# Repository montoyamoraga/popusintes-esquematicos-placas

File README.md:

# popusintes-esquematicos-placas

Parte de la tesis de Aarón Montoya-Moraga, en el Doctorado de Artes y Humanidades del Instituto de Estudios Avanzados de la Universidad de Santiago de Chile.

## Módulos

- [ataconso](./docs/ataconso.md)
- [chufe](./docs/chufe.md)
- [chufebu](./docs/chufebu.md)
- [diente](./docs/diente.md)
- [parla](./docs/parla.md)
- [relo](./docs/relo.md)
- [suma](https://github.com/piruetasxyz/suma): ahora en su propio repositorio.

## Desarrollo

Los esquemáticos y placas están hechos en KiCad. Para regenerar los BOM u otras exportaciones se usa un entorno virtual de Python:

```bash
python3 -m venv env
source env/bin/activate
pip install -r requirements.txt
```

`env/` está en `.gitignore`, así que hay que crearlo localmente antes de correr herramientas como `kicad-cli` o `easyeda2kicad`.

## Capturas y Bill of materials

Las capturas de esquemáticos y placas en [docs/images](./docs/images) y las tablas de Bill of materials en `docs/*.md` las genera [kicad-retrata](https://github.com/piruetasxyz/kicad-retrata) con GitHub Actions en cada push que cambia un archivo de KiCad. Los módulos y su revisión activa se configuran en [kicad-retrata.yml](./kicad-retrata.yml): para pasar un módulo a una nueva revisión basta con cambiar su `proyecto` ahí.

## Bibliotecas

Las bibliotecas de KiCad (símbolos, huellas y modelos 3D) están en [bibliotecas](./bibliotecas):

- [byom](./bibliotecas/byom): biblioteca BYOM (símbolos, huellas y modelos 3D de terceros).
- [easyeda2kicad.kicad_sym](./bibliotecas/easyeda2kicad.kicad_sym), [easyeda2kicad.pretty](./bibliotecas/easyeda2kicad.pretty) y [easyeda2kicad.3dshapes](./bibliotecas/easyeda2kicad.3dshapes): símbolos, huellas y modelos 3D convertidos desde EasyEDA con `easyeda2kicad`.

Hay que agregar `bibliotecas` como ruta de biblioteca en KiCad (Preferencias → Administrar bibliotecas de símbolos/huellas) para que los esquemáticos y placas encuentren estas piezas.

## Bloques reutilizables

[popusintes.kicad_blocks](./bibliotecas/popusintes.kicad_blocks) es una biblioteca de bloques de diseño (design blocks) de KiCad 10: fragmentos de circuito que se copian dentro de cada módulo, en vez de enlazarlos como hoja jerárquica compartida. Cada módulo queda con su propia copia, congelada en la versión con que se fabricó, así que cambiar un bloque no altera las revisiones ya hechas.

- [alimentacion-12v](./bibliotecas/popusintes.kicad_blocks/alimentacion-12v.kicad_block): conector eurorack 2x05 y diodos Schottky de protección contra polaridad inversa en ±12V.
- [alimentacion-12v-5v](./bibliotecas/popusintes.kicad_blocks/alimentacion-12v-5v.kicad_block): por ahora idéntico a `alimentacion-12v`; pensado para agregarle la rama de +5V.

Para usarlos:

1. Registrar la biblioteca en Preferencias → Administrar bibliotecas de bloques de diseño. La [plantilla](./plantillas/kicad/plantilla-popusintes) ya trae una tabla de proyecto (`design-block-lib-table`) que apunta a `${KIPRJMOD}/../../bibliotecas/popusintes.kicad_blocks`, válida para proyectos ubicados en `<modulo>/<modulo>-v-X-rev-Y/`.
2. En el editor de esquemáticos, abrir el panel de bloques de diseño y colocar el bloque, ya sea en línea o como hoja (_place as sheet_).
3. Para agregar o actualizar un bloque, seleccionar el circuito en un esquemático y guardarlo en la biblioteca desde el mismo panel.

Ataconso, que usaba la hoja compartida antigua, ahora tiene en [ataconso-v-0-rev-c](./ataconso/ataconso-v-0-rev-c) su propia copia de `fuente-alimentacion.kicad_sch` junto al proyecto. Parla y relo tienen la fuente de alimentación dibujada directamente en el esquemático.

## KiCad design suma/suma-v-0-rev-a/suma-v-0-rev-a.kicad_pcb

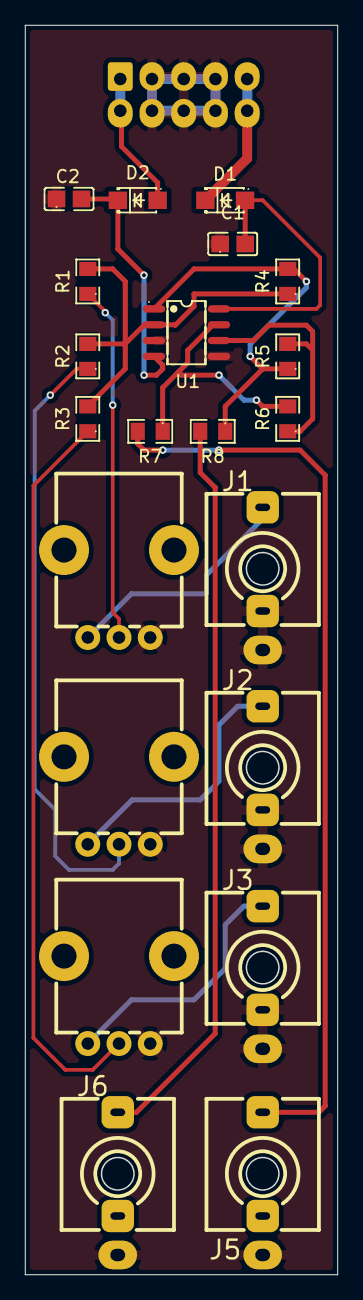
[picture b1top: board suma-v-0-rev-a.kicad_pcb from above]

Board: 2 copper layers, 25.0 x 100.0 mm, 22 parts (1 on the bottom side), 17 nets.

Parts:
C1, C2: 100n; C0805
D1, D2: 1N5817W; SOD-123FL_L2.8-W1.8-LS3.7-R-RD
J1, J2, J3, J5, J6: AudioJack2_SwitchT; Jack_3.5mm_QingPu_WQP-PJ398SM_Vertical
J4: Conn_02x05_Odd_Even; IDC-Header_2x05_P2.54mm_Vertical
R1, R2, R3, R4, R5, R6: 100k; R0805
R7, R8: 1k; R0805
RV1, RV2, RV3: A100k; POT_TH_Alps_RK09K_Single_Vertical
U1: TL072; SOIC-8_L4.9-W3.9-P1.27-LS6.0-BL

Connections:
+12V: C1.2, D1.1 (K), U1.8 (V+)
-12V: C2.2, D2.2 (A), U1.4 (V-)
GND: C1.1, C2.1, J1.1, J1.2, J2.1, J2.2, J3.1, J3.2, J4.3, J4.4, J4.5, J4.6, J4.7, J4.8, J5.1, J6.1, RV1.1, RV2.1, RV3.1, U1.3 (+), U1.5 (+)
unnamed: D1.2 (A), J4.9, J4.10
unnamed: D2.1 (K), J4.1, J4.2
unnamed: J1.3, RV1.3
unnamed: J2.3, RV2.3
unnamed: J3.3, RV3.3
unnamed: J5.3, R7.2
unnamed: J6.3, R8.2
unnamed: R1.1, RV1.2
unnamed: R2.1, RV2.2
unnamed: R3.1, RV3.2
unnamed: R4.2, R5.1, R8.1, U1.1
unnamed: R6.2, R7.1, U1.7
unnamed: R1.2, R2.2, R3.2, R4.1, U1.2 (-)
unnamed: R5.2, R6.1, U1.6 (-)

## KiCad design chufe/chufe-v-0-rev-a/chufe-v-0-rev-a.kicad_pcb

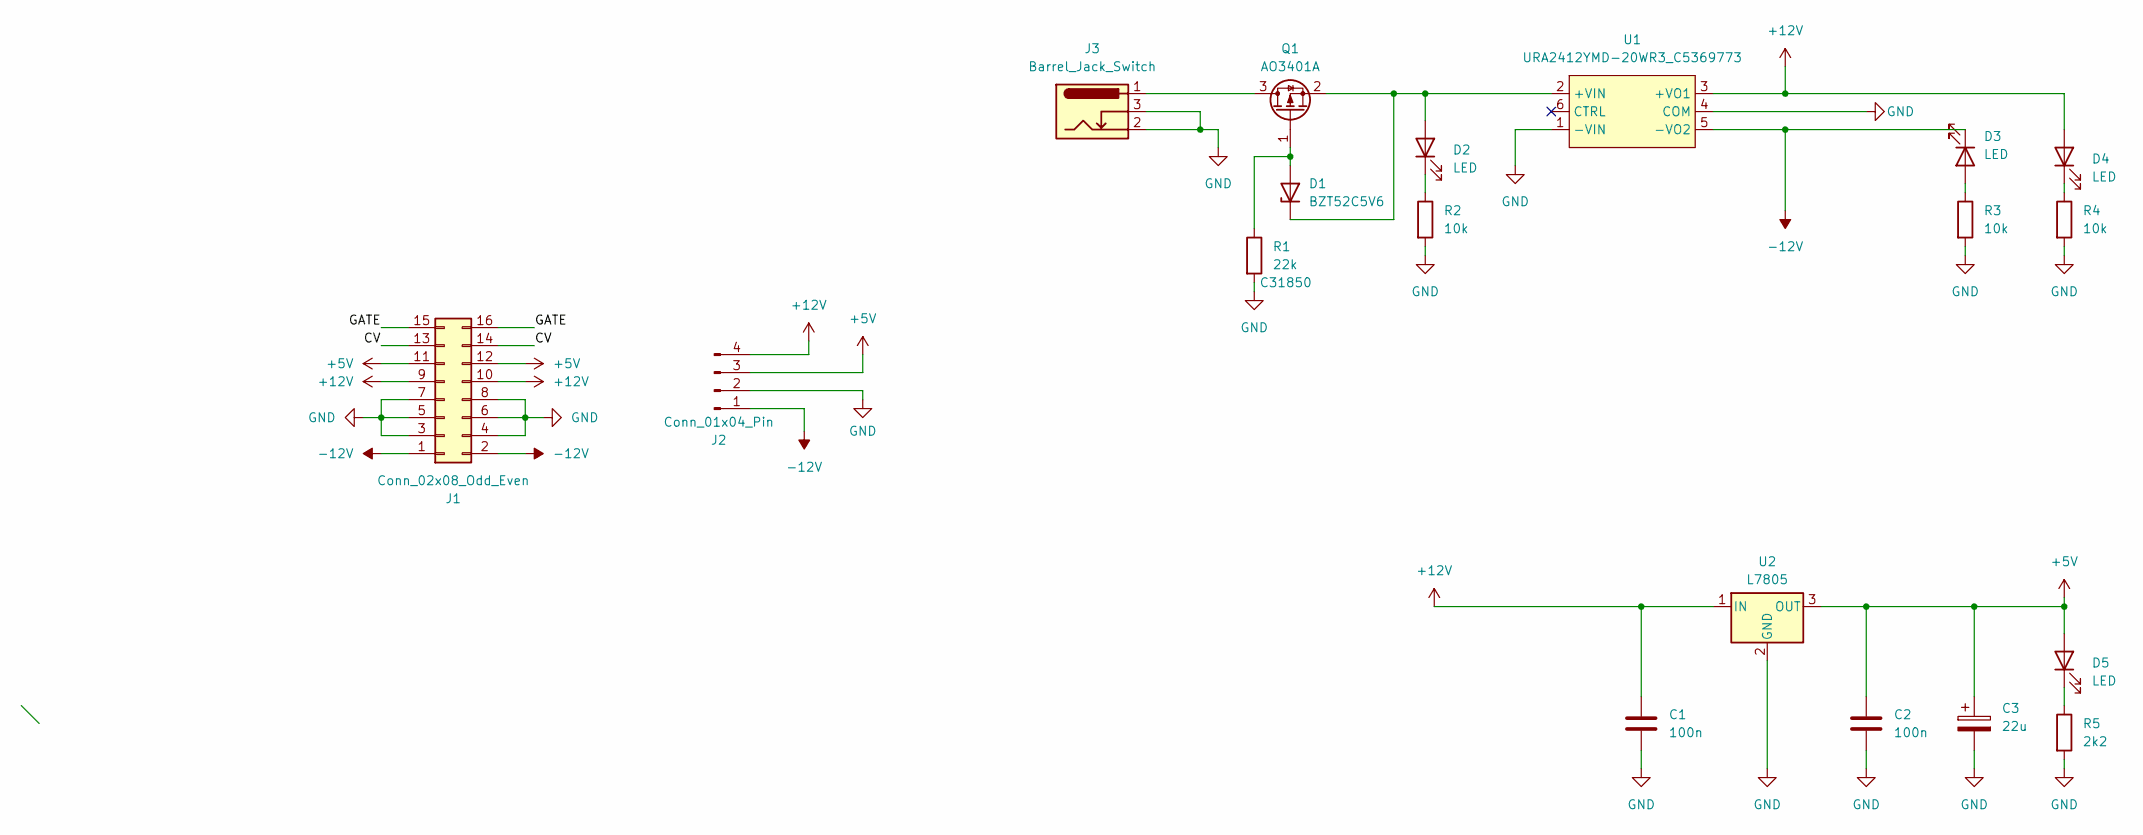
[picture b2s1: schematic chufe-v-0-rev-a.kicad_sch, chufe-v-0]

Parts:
C1, C2: 100n; C_0805_2012Metric
C3: 22u; CP_Elec_4x5.4
D1: BZT52C5V6; D_SOD-123; LCSC C19077402
D2, D3, D4, D5: LED; LED_D3.0mm
J1: Conn_02x08_Odd_Even; IDC-Header_2x08_P2.54mm_Vertical
J2: Conn_01x04_Pin; Molex_KK-396_5273-04A_1x04_P3.96mm_Vertical
J3: Barrel_Jack_Switch; BarrelJack_Horizontal
Q1: AO3401A; SOT-23
R1: 22k; R_0805_2012Metric; LCSC C31850
R2, R3, R4: 10k; R_0805_2012Metric
R5: 2k2; R_0805_2012Metric
U1: URA2412YMD-20WR3_C5369773; PWRM-TH_YLPTEC_VRBXXXXYMD-20WR3; MPN URA2412YMD-20WR3; LCSC Part C5369773
U2: L7805; TO-252-2

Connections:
+5V: C2.1, C3.1, D5.2 (A), J1.11, J1.12, J2.3, U2.3 (OUT)
+12V: C1.1, D4.2 (A), J1.9, J1.10, J2.4, U1.3 (+VO1), U2.1 (IN)
-12V: D3.1 (K), J1.1, J1.2, J2.1, U1.5 (-VO2)
/CV: J1.13, J1.14
/GATE: J1.15, J1.16
GND: C1.2, C2.2, C3.2, J1.3, J1.4, J1.5, J1.6, J1.7, J1.8, J2.2, J3.2, J3.3, R1.2, R2.2, R3.2, R4.2, R5.2, U1.1 (-VIN), U1.4 (COM), U2.2 (GND)
unnamed: D1.2 (A), Q1.1 (G), R1.1
unnamed: D1.1 (K), D2.2 (A), Q1.2 (S), U1.2 (+VIN)
unnamed: D2.1 (K), R2.1
unnamed: D3.2 (A), R3.1
unnamed: D4.1 (K), R4.1
unnamed: D5.1 (K), R5.1
unnamed: J3.1, Q1.3 (D)

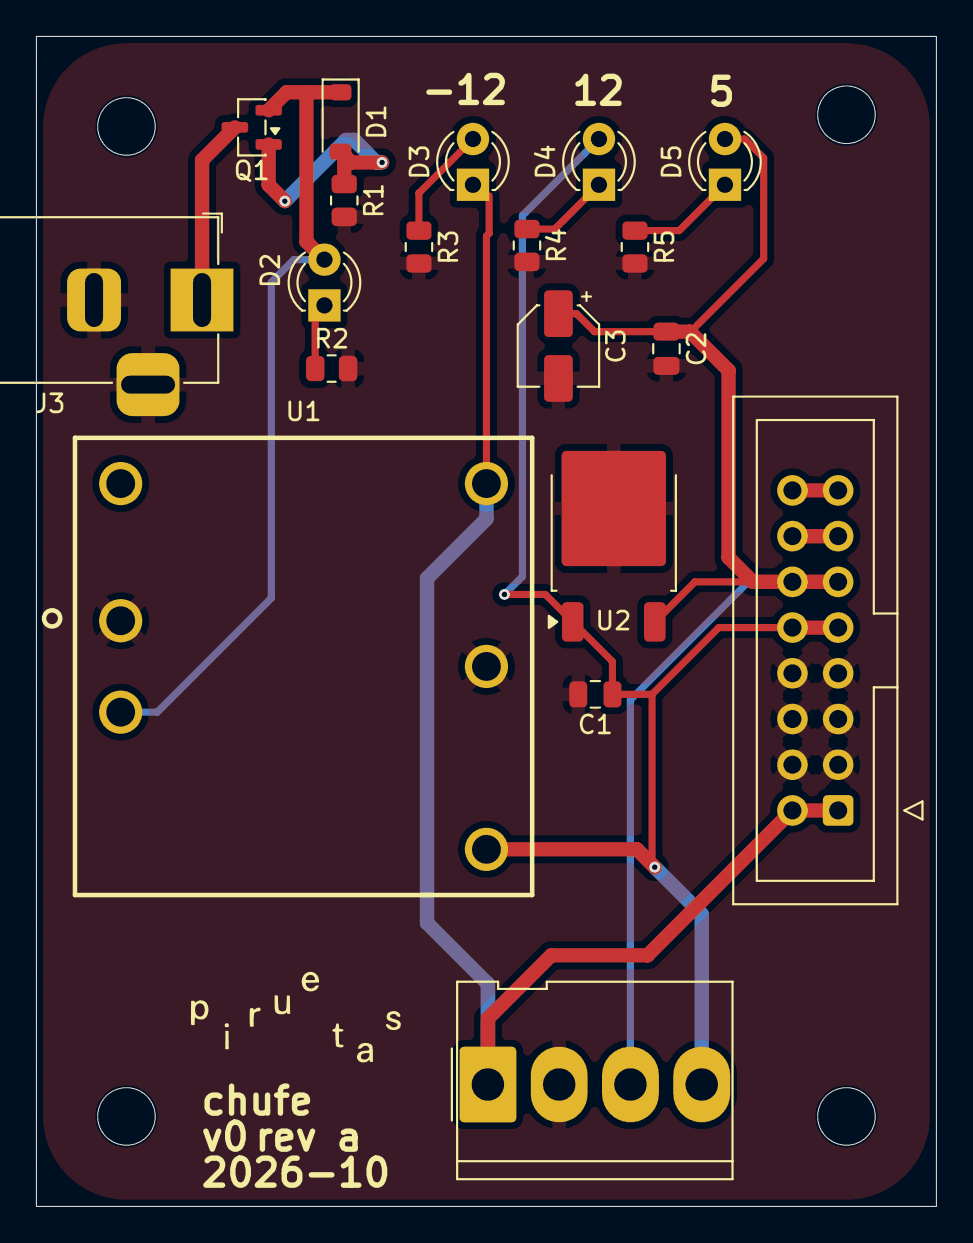
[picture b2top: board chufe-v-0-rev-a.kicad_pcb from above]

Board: 2 copper layers, 50.0 x 65.0 mm, 23 parts (0 on the bottom side), 13 nets.

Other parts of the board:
H1, H2, H3, H4: M3; MountingHole_3.2mm_M3

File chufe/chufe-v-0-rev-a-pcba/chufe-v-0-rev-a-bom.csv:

"Comment","Designator","Footprint","LCSC Part #"
"100n","C1,C2","Capacitor_SMD:C_0805_2012Metric","C49678"
"22u","C3","Capacitor_SMD:CP_Elec_4x5.4","C72502"
"BZT52C5V6","D1","Diode_SMD:D_SOD-123","C19077402"
"AO3401A","Q1","Package_TO_SOT_SMD:SOT-23","C15127"
"22k","R1","Resistor_SMD:R_0805_2012Metric","C31850"
"10k","R2,R3,R4","Resistor_SMD:R_0805_2012Metric","C17414"
"2k2","R5","Resistor_SMD:R_0805_2012Metric","C17520"
"URA2412YMD-20WR3_C5369773","U1","easyeda2kicad:PWRM-TH_YLPTEC_VRBXXXXYMD-20WR3","C5369773"
"L7805","U2","Package_TO_SOT_SMD:TO-252-2","C19626525"

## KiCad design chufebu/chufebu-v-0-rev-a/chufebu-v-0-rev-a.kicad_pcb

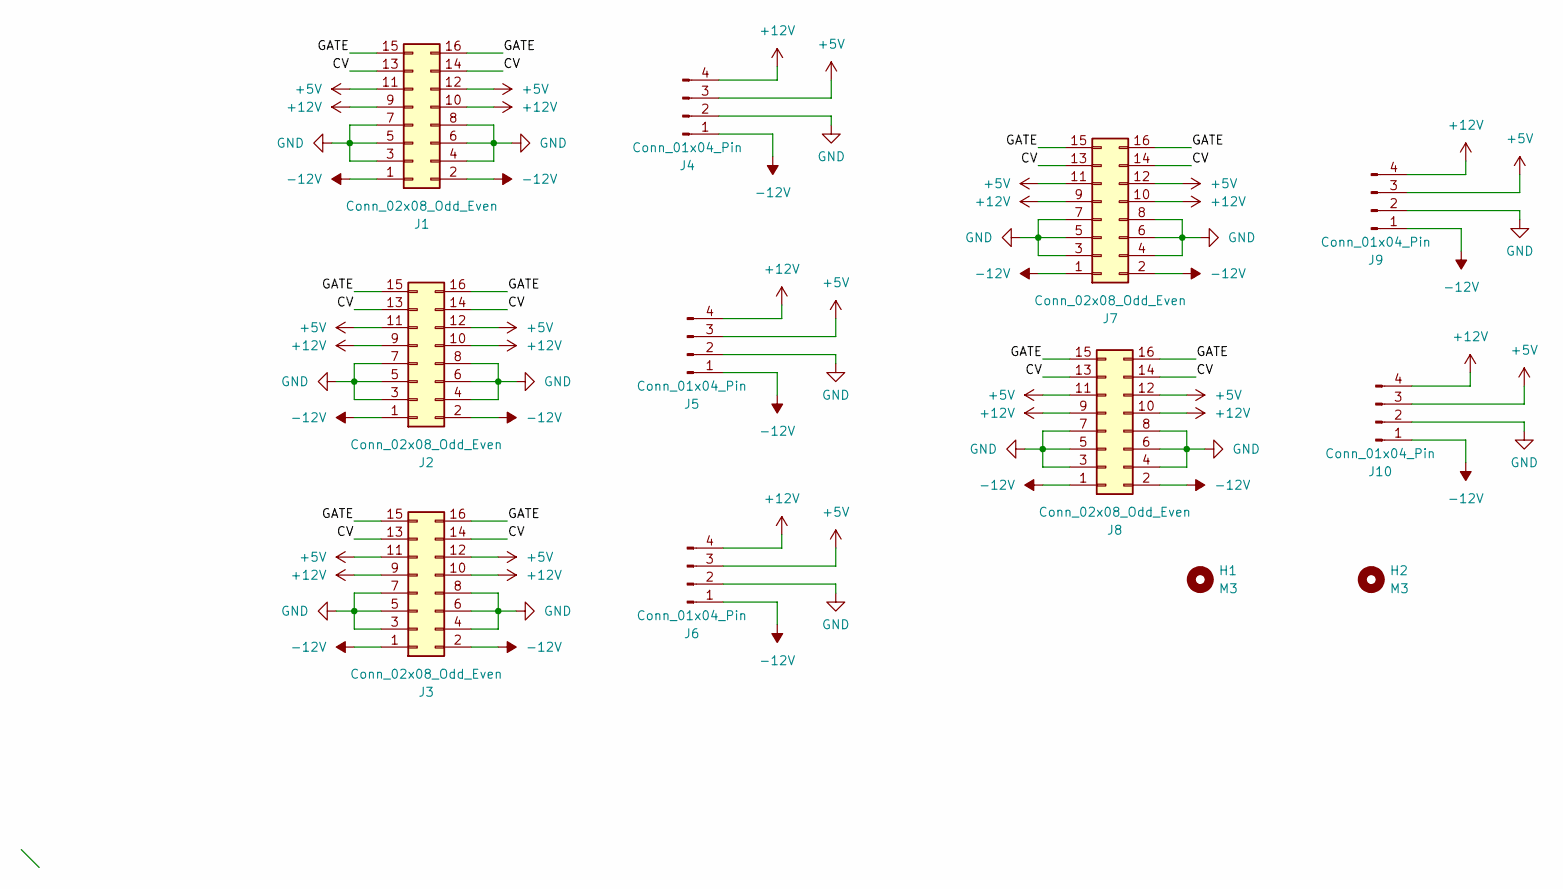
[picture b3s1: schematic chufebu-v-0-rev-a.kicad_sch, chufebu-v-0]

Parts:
H1, H2: M3; MountingHole_3.2mm_M3
J1, J2, J3, J7, J8: Conn_02x08_Odd_Even; IDC-Header_2x08_P2.54mm_Vertical
J4, J5, J6, J9, J10: Conn_01x04_Pin; Molex_KK-396_5273-04A_1x04_P3.96mm_Vertical

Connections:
+5V: J1.11, J1.12, J2.11, J2.12, J3.11, J3.12, J4.3, J5.3, J6.3, J7.11, J7.12, J8.11, J8.12, J9.3, J10.3
+12V: J1.9, J1.10, J2.9, J2.10, J3.9, J3.10, J4.4, J5.4, J6.4, J7.9, J7.10, J8.9, J8.10, J9.4, J10.4
-12V: J1.1, J1.2, J2.1, J2.2, J3.1, J3.2, J4.1, J5.1, J6.1, J7.1, J7.2, J8.1, J8.2, J9.1, J10.1
/CV: J1.13, J1.14, J2.13, J2.14, J3.13, J3.14, J7.13, J7.14, J8.13, J8.14
/GATE: J1.15, J1.16, J2.15, J2.16, J3.15, J3.16, J7.15, J7.16, J8.15, J8.16
GND: J1.3, J1.4, J1.5, J1.6, J1.7, J1.8, J2.3, J2.4, J2.5, J2.6, J2.7, J2.8, J3.3, J3.4, J3.5, J3.6, J3.7, J3.8, J4.2, J5.2, J6.2, J7.3, J7.4, J7.5, J7.6, J7.7, J7.8, J8.3, J8.4, J8.5, J8.6, J8.7, J8.8, J9.2, J10.2

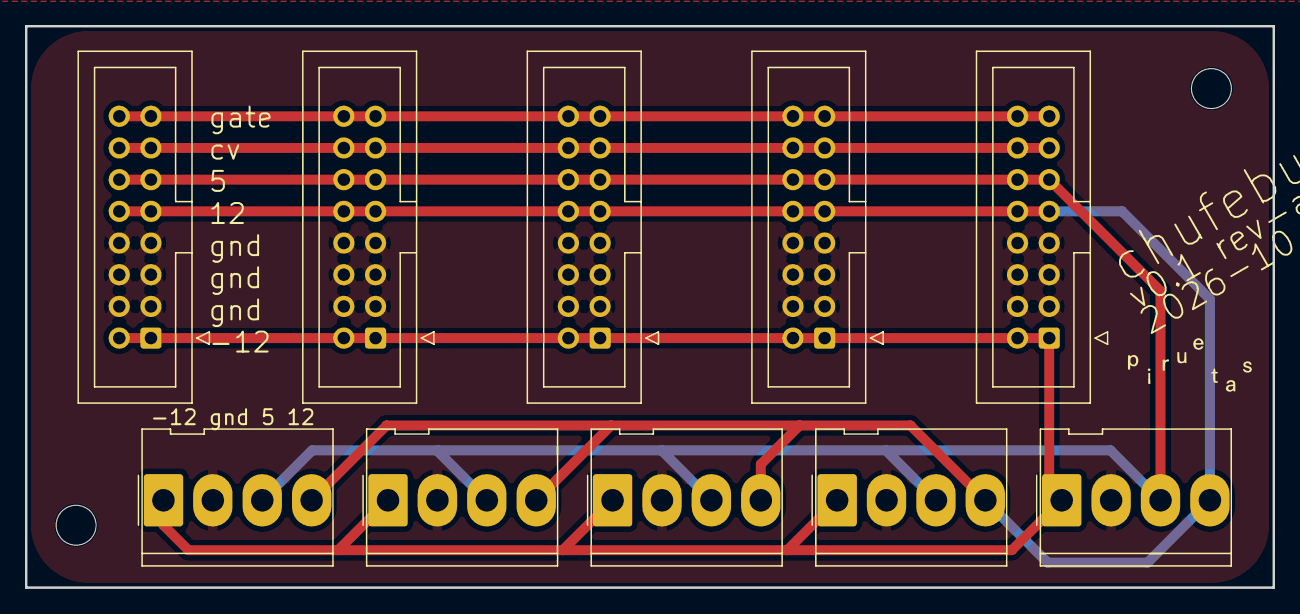
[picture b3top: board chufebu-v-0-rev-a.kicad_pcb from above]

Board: 2 copper layers, 100.0 x 45.0 mm, 12 parts (0 on the bottom side), 6 nets.

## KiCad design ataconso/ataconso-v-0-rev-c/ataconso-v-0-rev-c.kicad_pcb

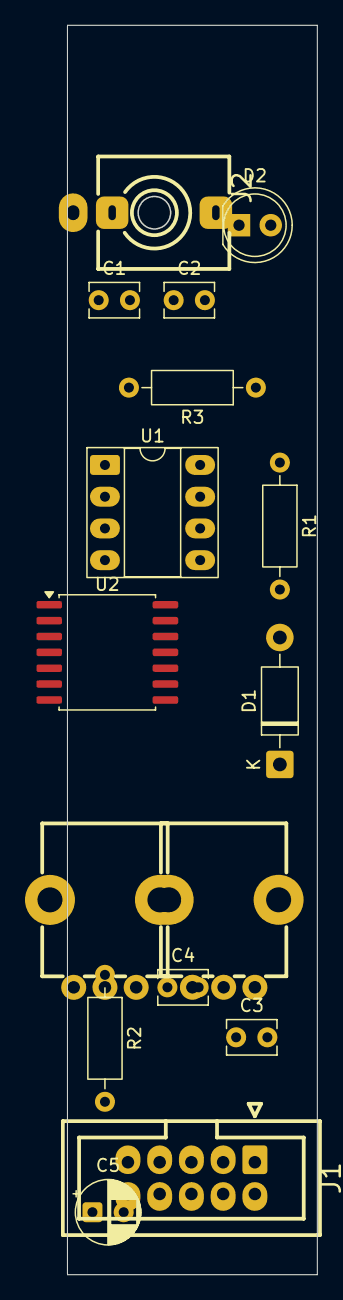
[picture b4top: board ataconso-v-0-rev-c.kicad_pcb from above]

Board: 2 copper layers, 20.0 x 100.0 mm, 16 parts (0 on the bottom side), 13 nets, no tracks yet.

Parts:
C1: 10n; C_Disc_D3.8mm_W2.6mm_P2.50mm
C2, C3, C4: 100n; C_Disc_D3.8mm_W2.6mm_P2.50mm
C5: 100n; CP_Radial_D5.0mm_P2.50mm
D1: 1N5817; D_DO-41_SOD81_P10.16mm_Horizontal
D2: 1N5817; LED_D5.0mm
J1: Conn_02x05_Odd_Even; IDC-Header_2x05_P2.54mm_Vertical
J2: AudioJack2_SwitchT; Jack_3.5mm_QingPu_WQP-PJ398SM_Vertical
R1: 10k; R_Axial_DIN0207_L6.3mm_D2.5mm_P10.16mm_Horizontal
R2: 1k; R_Axial_DIN0207_L6.3mm_D2.5mm_P10.16mm_Horizontal
R3: 100k; R_Axial_DIN0207_L6.3mm_D2.5mm_P10.16mm_Horizontal
RV1, RV2: 470k; POT_TH_Alps_RK09K_Single_Vertical
U1: TL072; DIP-8_W7.62mm_Socket_LongPads
U2: NA556; SOIC-14W_7.5x9mm_P1.27mm

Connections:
+12V: C3.1, D1.1 (K), R1.1, RV2.2, U1.8 (V+), U2.4 (~RST), U2.10 (~RST), U2.14 (VCC)
-12V: C4.1, D2.2 (A), U1.4 (V-)
GND: C1.2, C2.2, C3.2, C4.2, C5.2, J1.3, J1.4, J1.5, J1.6, J1.7, J1.8, R3.2, U1.2 (-), U1.3 (+), U2.7 (GND)
unnamed: D1.2 (A), J1.9, J1.10
unnamed: D2.1 (K), J1.1, J1.2
unnamed: R2.1, RV2.3
unnamed: R3.1, U1.5 (+)
unnamed: U1.6 (-), U1.7
unnamed: C2.1, U2.3 (CONT)
unnamed: R1.2, RV1.2, U2.1 (DISCH)
unnamed: U2.5 (OUT), U2.8 (TRIG)
unnamed: C1.1, RV1.3, U2.2 (THRES), U2.6 (TRIG)
unnamed: C5.1, R2.2, U2.12 (THRES), U2.13 (DISCH)

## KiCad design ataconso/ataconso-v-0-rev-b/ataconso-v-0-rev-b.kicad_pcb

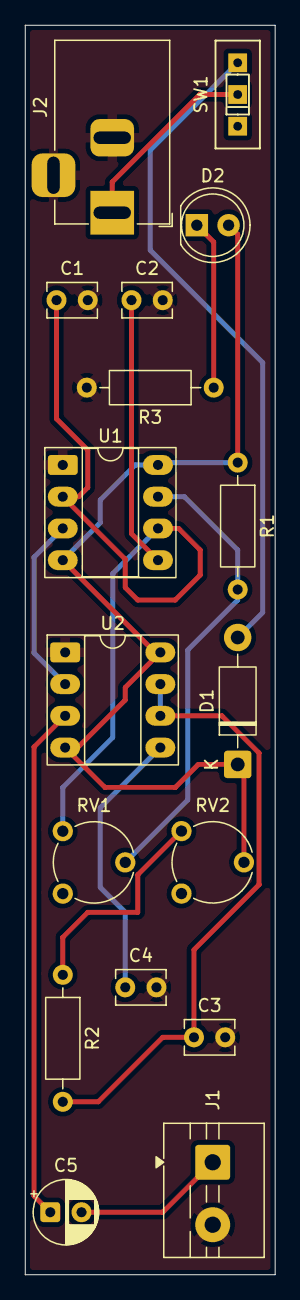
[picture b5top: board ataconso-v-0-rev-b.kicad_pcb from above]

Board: 2 copper layers, 20.0 x 100.0 mm, 17 parts (0 on the bottom side), 14 nets.

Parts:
C1: 10n; C_Disc_D3.8mm_W2.6mm_P2.50mm
C2, C3, C4: 100n; C_Disc_D3.8mm_W2.6mm_P2.50mm
C5: 100u; CP_Radial_D5.0mm_P2.50mm
D1: 1n4007; D_DO-41_SOD81_P10.16mm_Horizontal
D2: LED; LED_D5.0mm
J1: Screw_Terminal_01x02; TerminalBlock_MaiXu_MX126-5.0-02P_1x02_P5.00mm
J2: Barrel_Jack_Switch; BarrelJack_Horizontal
R1: 10k; R_Axial_DIN0207_L6.3mm_D2.5mm_P10.16mm_Horizontal
R2, R3: 1k; R_Axial_DIN0207_L6.3mm_D2.5mm_P10.16mm_Horizontal
RV1, RV2: 470k; Potentiometer_Piher_PT-6-V_Vertical
SW1: SW_SPDT; spdt_ssd12d00g3
U1, U2: NE555D; DIP-8_W7.62mm_Socket_LongPads

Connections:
GND: C1.2, C2.2, C3.2, C4.2, J1.2, J2.2, J2.3, R3.2, U1.1 (GND), U2.1 (GND)
unnamed: D1.2 (A), SW1.3 (C)
unnamed: D2.1 (K), R3.1
unnamed: C5.2, J1.1
unnamed: R2.1, RV2.3
unnamed: J2.1, SW1.2 (B)
unnamed: C2.1, U1.5 (CONT)
unnamed: R1.2, RV1.2, U1.7 (DISCH)
unnamed: U1.3 (OUT), U2.2 (TRIG)
unnamed: C1.1, RV1.3, U1.2 (TRIG), U1.6 (THRES)
unnamed: C4.1, U2.5 (CONT)
unnamed: C3.1, R2.2, U2.6 (THRES), U2.7 (DISCH)
unnamed: C5.1, U2.3 (OUT)
VCC: D1.1 (K), D2.2 (A), R1.1, RV2.2, U1.4 (~RST), U1.8 (VCC), U2.4 (~RST), U2.8 (VCC)

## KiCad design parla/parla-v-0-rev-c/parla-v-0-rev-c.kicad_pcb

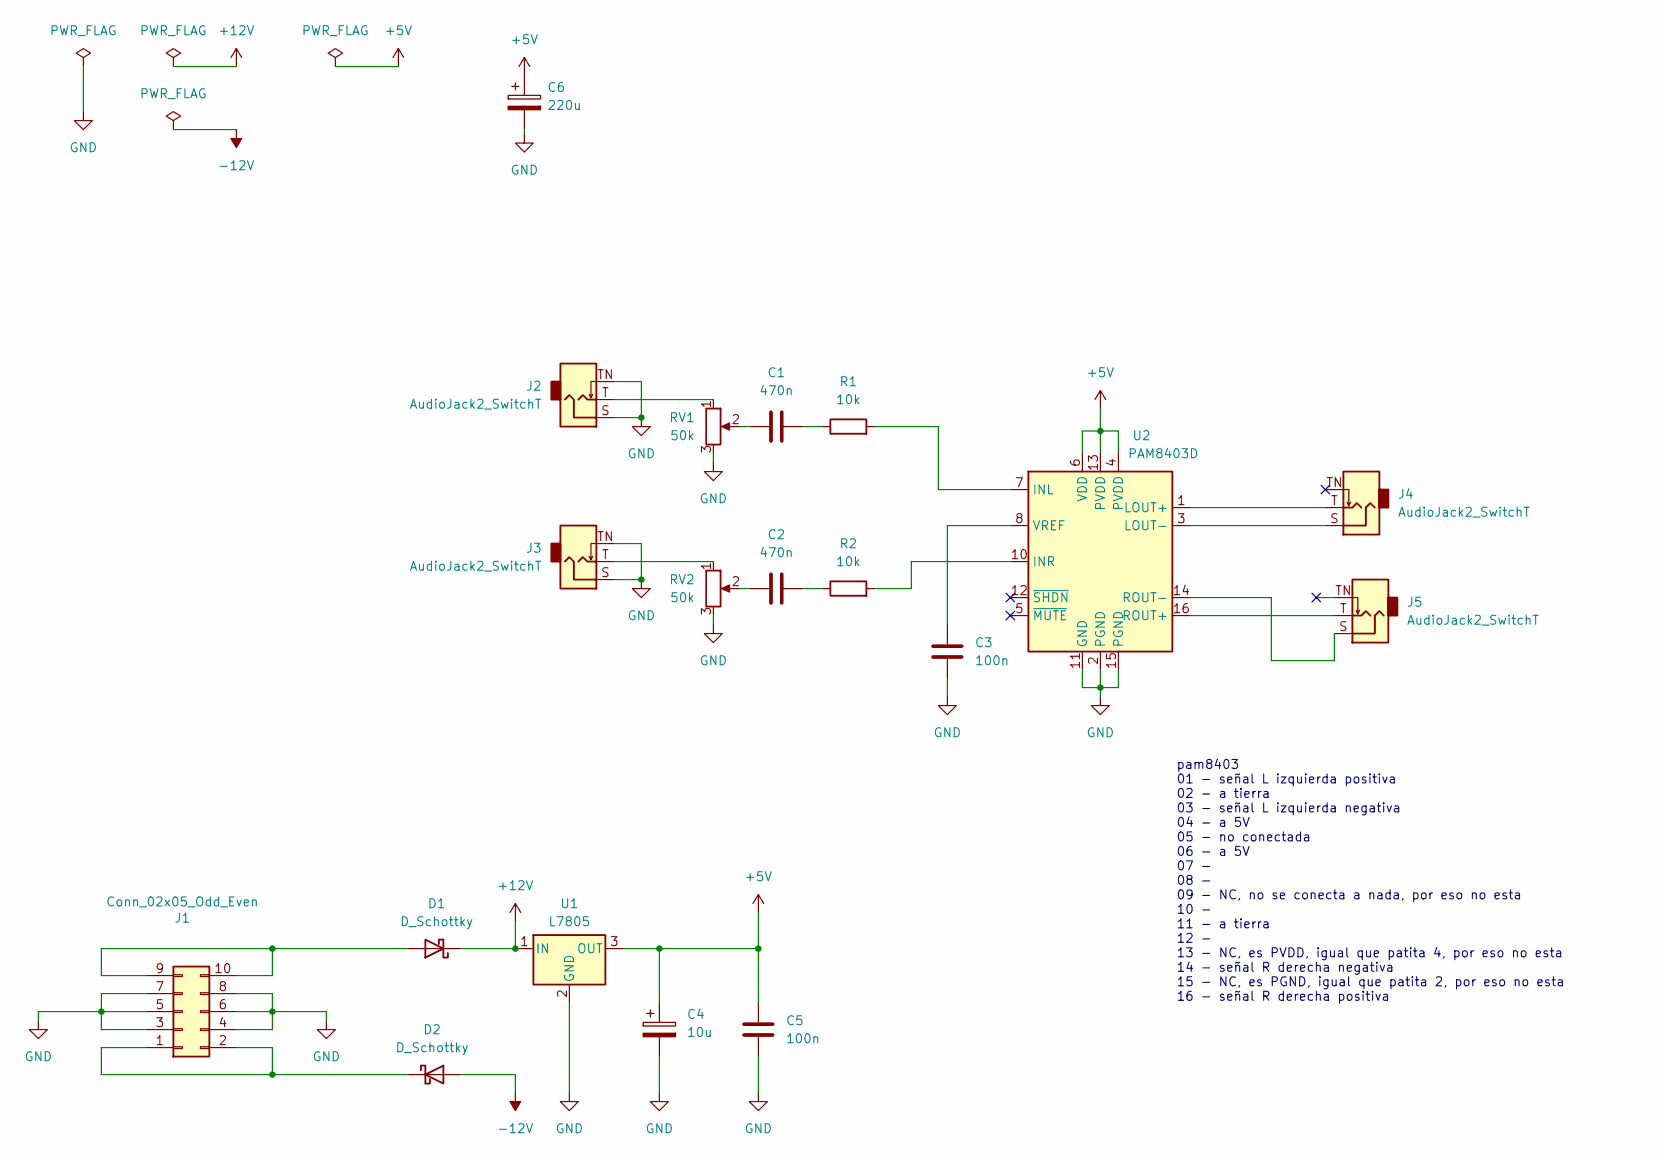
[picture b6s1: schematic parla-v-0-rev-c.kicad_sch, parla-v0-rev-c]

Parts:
C1, C2: 470n; C_Elec_4x5.4; LCSC C2895732
C3, C5: 100n; C_0805_2012Metric_Pad1.18x1.45mm_HandSolder; LCSC C49678
C4: 10u; CP_Elec_4x5.4; LCSC C3357
C6: 220u; CP_Elec_6.3x7.7; LCSC C3342
D1, D2: D_Schottky; SOD-123FL_L2.8-W1.8-LS3.7-R-RD
J1: Conn_02x05_Odd_Even; IDC-Header_2x05_P2.54mm_Vertical
J2, J3, J4, J5: AudioJack2_SwitchT; Jack_3.5mm_QingPu_WQP-PJ398SM_Vertical
R1, R2: 10k; R_0805_2012Metric_Pad1.20x1.40mm_HandSolder; LCSC C17414
RV1, RV2: 50k; POT_TH_Alps_RK09K_Single_Vertical
U1: L7805; TO-252-2; LCSC C19626525
U2: PAM8403D; SOP-16_4.4x10.4mm_P1.27mm; LCSC C5122557

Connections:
+5V: C4.1, C5.1, C6.1, U1.3 (OUT), U2.4 (PVDD), U2.6 (VDD), U2.13 (PVDD)
+12V: D1.1 (K), U1.1 (IN)
-12V: D2.2 (A)
GND: C3.2, C4.2, C5.2, C6.2, J1.3, J1.4, J1.5, J1.6, J1.7, J1.8, J2.S, J2.TN, J3.S, J3.TN, RV1.3, RV2.3, U1.2 (GND), U2.2 (PGND), U2.11 (GND), U2.15 (PGND)
unnamed: C1.1, RV1.2
unnamed: C1.2, R1.1
unnamed: C2.1, RV2.2
unnamed: C2.2, R2.1
unnamed: D1.2 (A), J1.9, J1.10
unnamed: D2.1 (K), J1.1, J1.2
unnamed: J2.T, RV1.1
unnamed: J3.T, RV2.1
unnamed: R1.2, U2.7 (INL)
unnamed: R2.2, U2.10 (INR)
unnamed: J4.T, U2.1 (LOUT+)
unnamed: J4.S, U2.3 (LOUT-)
unnamed: J5.T, U2.16 (ROUT+)
unnamed: J5.S, U2.14 (ROUT-)
unnamed: C3.1, U2.8 (VREF)

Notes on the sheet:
pam8403 01 - señal L izquierda positiva 02 - a tierra 03 - señal L izquierda negativa 04 - a 5V 05 - no conectada 06 - a 5V 07 - 08 - 09 - NC, no se conecta a nada, por eso no esta 10 - 11 - a tierra 12 - 13 - NC, es PVDD, igual que patita 4, por eso no esta 14 - señal R derecha negativa 15 - NC, e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

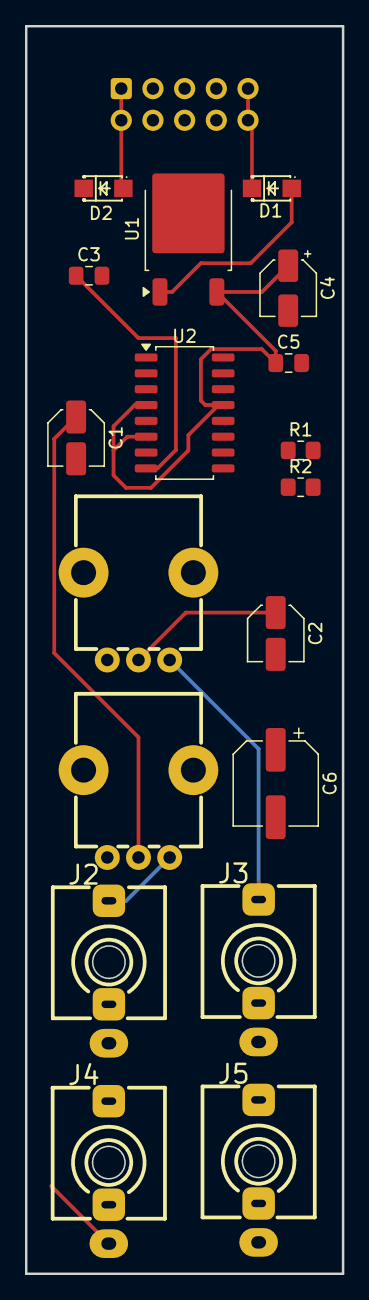
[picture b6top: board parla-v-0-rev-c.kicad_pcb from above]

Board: 2 copper layers, 25.4 x 100.0 mm, 19 parts (1 on the bottom side), 18 nets.
